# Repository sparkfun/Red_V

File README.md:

SparkFun RED-V RedBoard
============================

*[SparkFun RED-V RedBoard (DEV-15594)](https://www.sparkfun.com/products/15594)*

The SparkFun RED-V (pronounced “red-five”) RedBoard is a low-cost, development board featuring the Freedom E310 SoC which brings with it the RISC-V instruction set architecture (ISA). What sets the RED-V RedBoard apart from the rest is the completely open-source approach from hardware to ISA. That means anyone can make full use the microcontroller without requiring royalties, licenses, or non-disclosure agreements. 

The RED-V RedBoard comes in the familiar Arduino Uno R3 form factor and includes the SiFive Freedom E310 core, 32MB of QSPI flash, an NXP K22 ARM Cortex-M4 for USB connectivity and operating as a JTAG interface, and a Qwiic connector to make I<sup>2</sup>C easy. The modern USB-C connector makes it easy to program and for more advanced users who prefer to use the power and speed of professional tools, we've also exposed the JTAG connector. Additionally, it comes programmed with a simple bootloader making the RED-V the best way to start prototyping and developing your RISC‑V applications. 

The on board Freedom E310 (FE310) is the first member of the Freedom Everywhere family of customizable SoCs from SiFive. Designed for microcontroller, embedded, IoT, and wearable applications, the FE310 features SiFive’s E31 CPU Coreplex, a high-performance, 32-bit RV32IMAC core. Running at 320+ MHz, the FE310 is among the fastest microcontrollers in the market. Additional features include a 16KB L1 Instruction Cache, a 16KB Data SRAM scratchpad, hardware multiply/divide, a debug module, flexible clock generation with on-chip oscillators and PLLs, and a wide variety of peripherals including UARTs, QSPI, PWMs, and timers. Multiple power domains and a low-power standby mode ensure a wide variety of applications can benefit from the FE310. The RED-V requires Freedom Studio software or a Zephyr RTOS build environment set up to program the board and interface with it.

Repository Contents
-------------------
* **/Hardware** - Eagle design files (.brd, .sch)
* **/Production** - Production panel files (.brd)

Documentation
--------------
* **[Hookup Guide](https://learn.sparkfun.com/tutorials/red-v-redboard-hookup-guide)** - Basic hookup guide for the RedBoard.
* **[RED-V Development Guide](https://learn.sparkfun.com/tutorials/red-v-development-guide)** - Getting started with the RED-V in Freedom Studio and Zephyr RTOS.

License Information
-------------------

This product is _**open source**_! 

Please review the LICENSE.md file for license information. 

If you have any questions or concerns on licensing, please contact techsupport@sparkfun.com.

Distributed as-is; no warranty is given.

- Your friends at SparkFun.

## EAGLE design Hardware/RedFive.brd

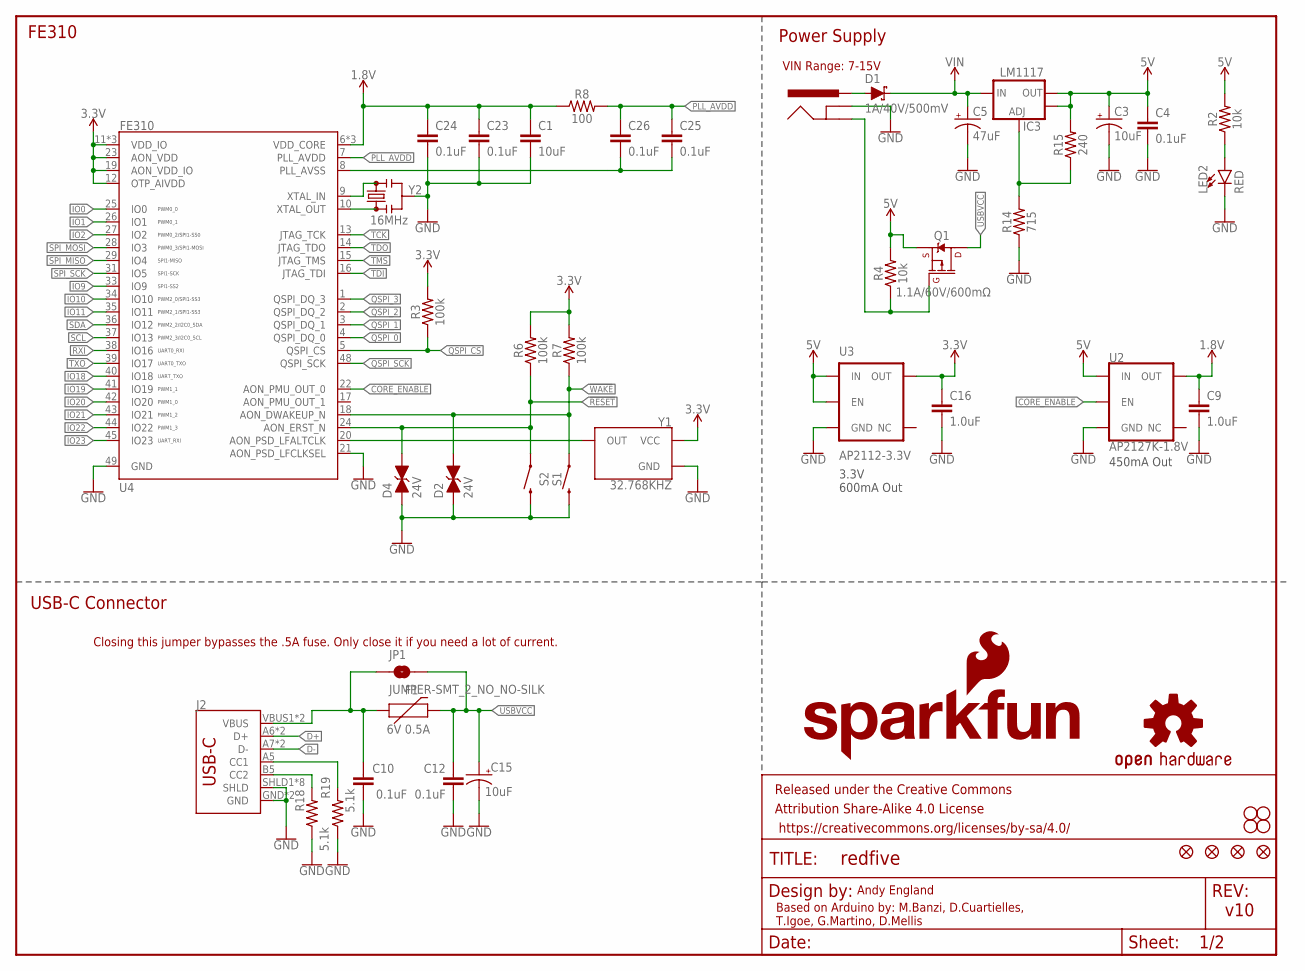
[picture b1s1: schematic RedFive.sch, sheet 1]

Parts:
C1: 10uF; 0603
C3, C15: 10uF; EIA3216
C4, C10, C12, C23, C24, C25, C26: 0.1uF; 0603
C5: 47uF; PANASONIC_D
C9, C16: 1.0uF; 0603
D1: 1A/40V/500mV; SMA-DIODE
D2, D4: 24V; 0603
F1: 6V 0.5A; 0805
FRAME2: FRAME-LETTER; CREATIVE_COMMONS
IC3: LM1117; SOT223-ALT1
J2: USB Female Type C Connector; USB-C-16P
J3: POWER_JACKSUPER_BOMB_DIGITY; POWER_JACK_SMD_OVERPASTE_SUPER_BOMB_DIGITY
JP1: JUMPER-SMT_2_NO_NO-SILK; SMT-JUMPER_2_NO_NO-SILK
JP3, JP4, JP5, JP6: STAND-OFF
JP8, JP9, JP15, JP16: FIDUCIAL1X2; FIDUCIAL-1X2
LED2: RED; LED-1206
LOGO1: SFE_LOGO_NAME_FLAME.1_INCH; SFE_LOGO_NAME_FLAME_.1
Q1: 1.1A/60V/600mΩ; SOT23-3
R2, R4: 10k; 0603
R3, R6, R7: 100k; 0603
R8: 100; 0603
R14: 715; 0603
R15: 240; 0603
R18, R19: 5.1k; 0603
S1, S2: MOMENTARY-SWITCH-SPST-SMD-6.2MM-TALL; TACTILE_SWITCH_SMD_6.2MM_TALL
U2: AP2127K-1.8V; SOT23-5
U3: AP2112-3.3V; SOT23-5
U4: FE310; QFN-48-.4MMPITCH
U$16: OSHW-LOGOS; OSHW-LOGO-S
Y1: 32.768KHZ; CRYSTAL-SMD-2X1.2MM
Y2: 16MHz; RESONATOR-SMD-3.2X1.3

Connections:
1.8V: C1.1, C9.1, C23.1, C24.1, R8.1, U2.5 (OUT), U4.6 (VDD_CORE), U4.30 (VDD_CORE), U4.46 (VDD_CORE)
3.3V: C16.1, R3.2, R6.2, R7.2, U3.5 (OUT), U4.11 (VDD_IO), U4.12 (OTP_AIVDD), U4.19 (AON_VDD_IO), U4.23 (AON_VDD), U4.32 (VDD_IO), U4.47 (VDD_IO), Y1.4 (VCC); also elsewhere on the board
5V: C3.+, C4.1, IC3.2 (OUT), IC3.4 (OUT), Q1.2 (S), R2.2, R4.2, R15.2, U2.1 (IN), U3.1 (IN), U3.3 (EN); also elsewhere on the board
!RESET: D4.2 (C), R6.1, S2.A2 (1), U4.24 (AON_ERST_N); also elsewhere on the board
!WAKE: D2.2 (C), R7.1, S1.A2 (1), U4.18 (AON_DWAKEUP_N); also elsewhere on the board
CORE_ENABLE: U2.3 (EN), U4.22 (AON_PMU_OUT_0)
D+: J2.A6 (D+), J2.B6 (D+); also elsewhere on the board
D-: J2.A7 (D-), J2.B7 (D-); also elsewhere on the board
GND: C1.2, C3.-, C4.2, C5.-, C9.2, C10.2, C12.2, C15.-, C16.2, C23.2, C24.2, D2.1 (A), D4.1 (A), J2.GND, J2.GND2 (GND), J2.SHLD1 (SHLD), J2.SHLD2 (SHLD), J2.SHLD3 (SHLD), J2.SHLD4 (SHLD), J2.SHLD5 (SHLD), J2.SHLD6 (SHLD), J2.SHLD7 (SHLD), J2.SHLD8 (SHLD), J3.GND (GNDBREAK), LED2.C, R14.1, R18.1, R19.1, S1.B2 (2), S2.B2 (2), U2.2 (GND), U3.2 (GND), U4.21 (AON_PSD_LFCLKSEL), U4.49 (GND), Y1.2 (GND), Y2.2; also elsewhere on the board
INSERT: J3.P$4 (GND), Q1.1 (G), R4.1
IO0: U4.25 (IO0); also elsewhere on the board
IO1: U4.26 (IO1); also elsewhere on the board
IO2: U4.27 (IO2); also elsewhere on the board
IO9: U4.33 (IO9); also elsewhere on the board
IO10: U4.34 (IO10); also elsewhere on the board
IO11: U4.35 (IO11); also elsewhere on the board
IO18: U4.40 (IO18); also elsewhere on the board
IO19: U4.41 (IO19); also elsewhere on the board
IO20: U4.42 (IO20); also elsewhere on the board
IO21: U4.43 (IO21); also elsewhere on the board
IO22: U4.44 (IO22); also elsewhere on the board
IO23: U4.45 (IO23); also elsewhere on the board
unnamed: LED2.A, R2.1
unnamed: U4.10 (XTAL_OUT), Y2.1
unnamed: U4.9 (XTAL_IN), Y2.3
unnamed: U4.20 (AON_PSD_LFALTCLK), Y1.3 (OUT)
unnamed: C25.2, C26.2, U4.8 (PLL_AVSS)
unnamed: J2.B5 (CC2), R18.2
unnamed: IC3.1 (ADJ), R14.2, R15.1
unnamed: J2.A5 (CC1), R19.2
PLL_AVDD: C25.1, C26.1, R8.2, U4.7 (PLL_AVDD)
PWRIN: D1.A, J3.VIN0 (PWR)
QSPI_0: U4.4 (QSPI_DQ_0); also elsewhere on the board
QSPI_1: U4.3 (QSPI_DQ_1); also elsewhere on the board
QSPI_2: U4.2 (QSPI_DQ_2); also elsewhere on the board
QSPI_3: U4.1 (QSPI_DQ_3); also elsewhere on the board
QSPI_CS: R3.1, U4.5 (QSPI_CS); also elsewhere on the board
QSPI_SCK: U4.48 (QSPI_SCK); also elsewhere on the board
RXI: U4.38 (IO16); also elsewhere on the board
SCL: U4.37 (IO13); also elsewhere on the board
SDA: U4.36 (IO12); also elsewhere on the board
SPI_MISO: U4.29 (IO4); also elsewhere on the board
SPI_MOSI: U4.28 (IO3); also elsewhere on the board
SPI_SCK: U4.31 (IO5); also elsewhere on the board
TCK: U4.13 (JTAG_TCK); also elsewhere on the board
TDI: U4.16 (JTAG_TDI); also elsewhere on the board
TDO: U4.14 (JTAG_TDO); also elsewhere on the board
TMS: U4.15 (JTAG_TMS); also elsewhere on the board
TXO: U4.39 (IO17); also elsewhere on the board
USBVCC: C12.1, C15.+, F1.2, JP1.2, Q1.3 (D)
VIN: C5.+, D1.C, IC3.3 (IN); also elsewhere on the board
VUSB: C10.1, F1.1, J2.VBUS1 (VBUS), J2.VBUS2 (VBUS), JP1.1

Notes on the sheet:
Power Supply
FE310
USB-C Connector
Based on Arduino by: M.Banzi, D.Cuartielles, T.Igoe, G.Martino, D.Mellis
Andy England
v10
VIN Range: 7-15V
3.3V 600mA Out
450mA Out
Closing this jumper bypasses the .5A fuse. Only close it if you need a lot of current.

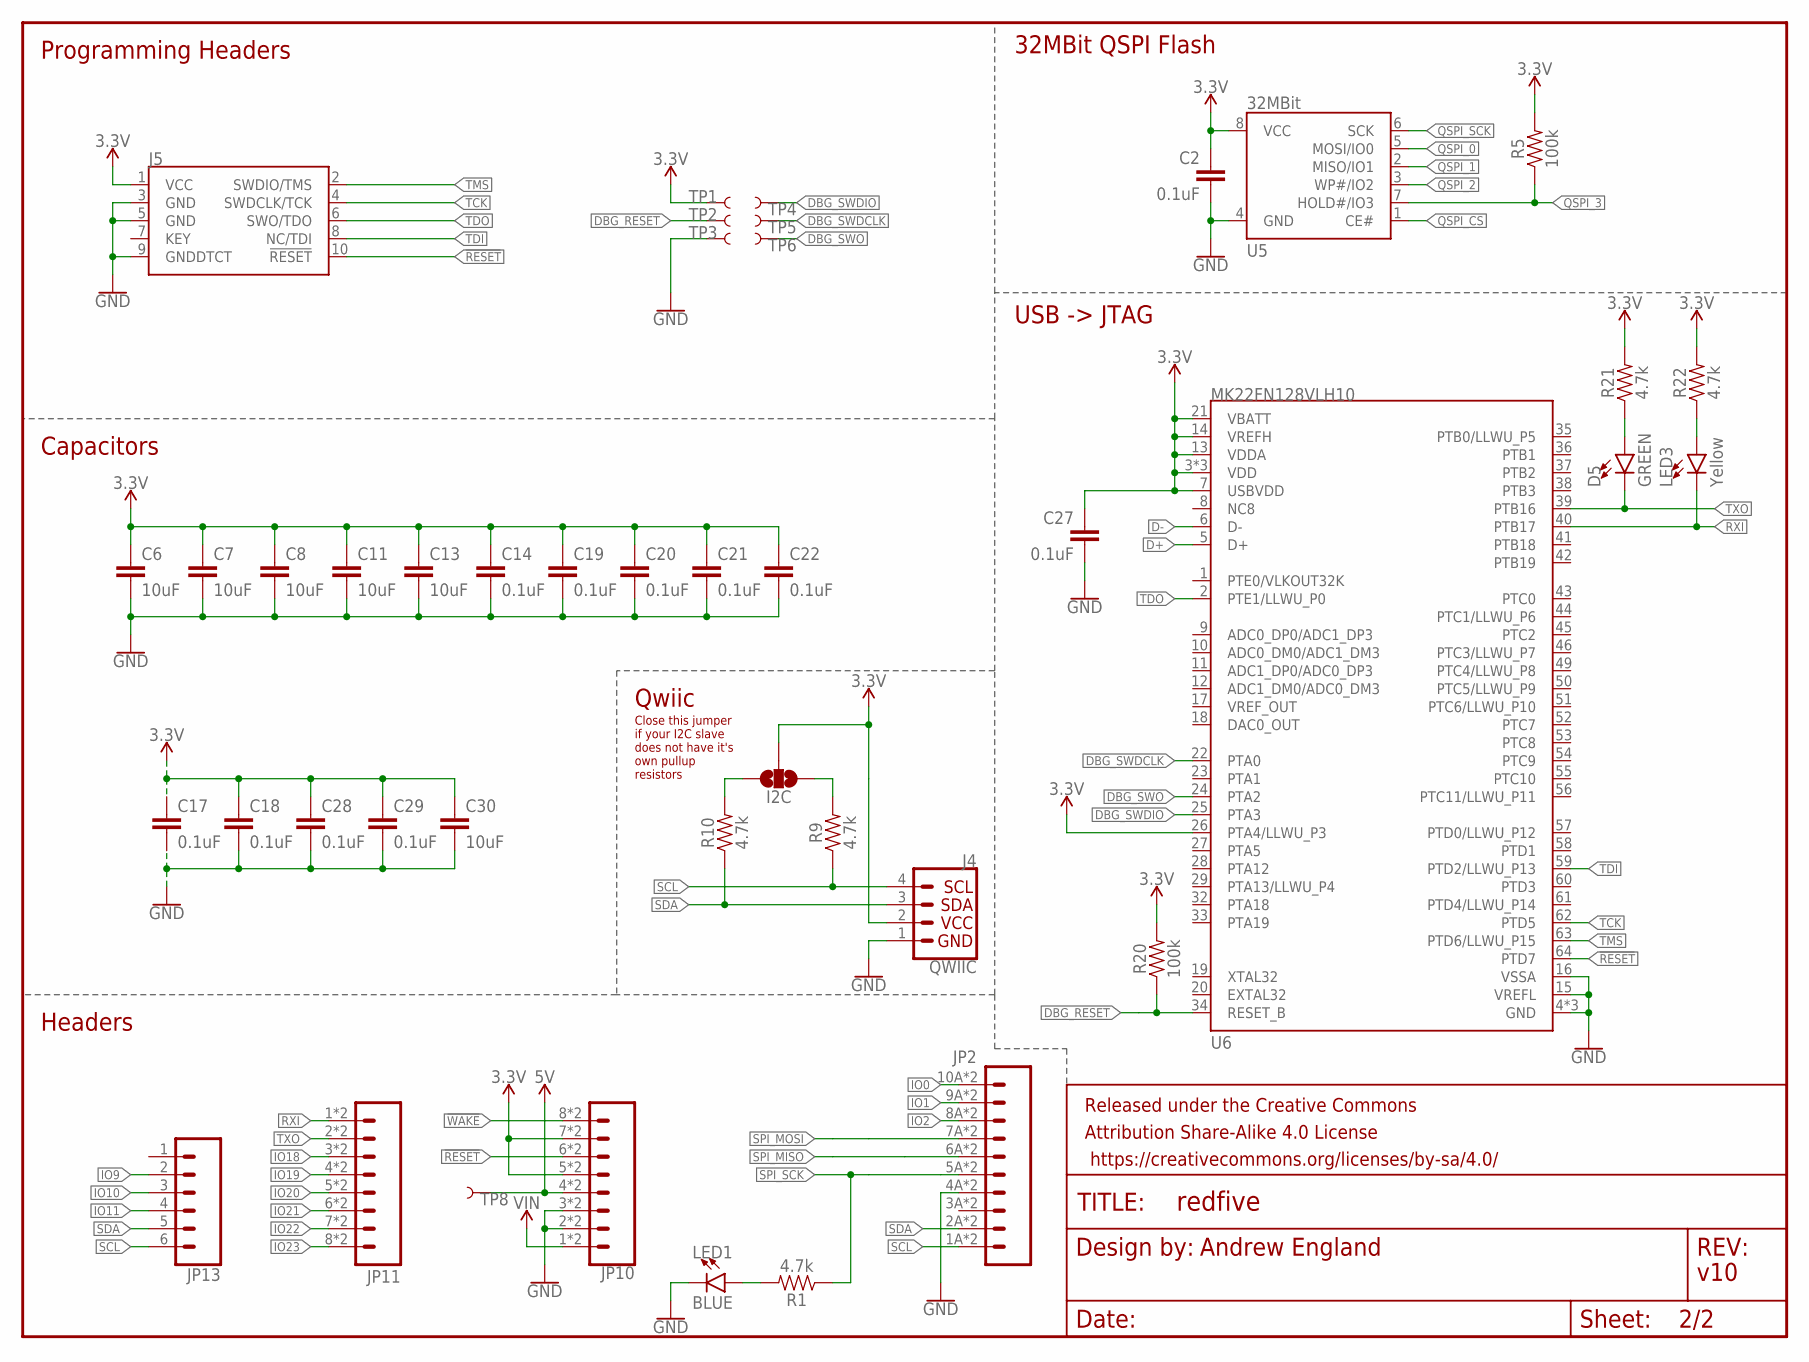
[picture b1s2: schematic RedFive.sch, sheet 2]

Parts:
C2, C14, C17, C18, C19, C20, C21, C22, C27, C28, C29: 0.1uF; 0603
C6, C7, C8, C11, C13, C30: 10uF; 0603
D5: GREEN; LED-1206
FRAME1: FRAME-LETTER; CREATIVE_COMMONS
I2C: JUMPER-SMT_3_NO_NO-SILK; SMT-JUMPER_3_NO_NO-SILK
J4: QWIIC; JST04_1MM_RA
J5: CORTEX_JTAG_DEBUG_PTH_NS; 2X5-PTH-1.27MM-NO_SILK
JP2: CONN_10SMD_COMBO-FEMALE; 1X10_SMD_COMBINED
JP10: CONN_08SMD-COMBO-FEMALE; 1X08_SMD_COMBINED
JP11: JP11; 1X08_SMD_COMBINED
JP13: CONN_06SMD-STRAIGHT-COMBO-FEMALE; 1X06_SMD_STRAIGHT_COMBO
LED1: BLUE; LED-1206
LED3: Yellow; LED-1206
R1, R9, R10, R21, R22: 4.7k; 0603
R5, R20: 100k; 0603
TP1, TP2, TP3, TP4, TP5, TP6: TEST-POINT3X5; PAD.03X.05
TP8: TEST-POINT3; PAD.03X.03
U5: 32MBit; SO08
U6: MK22FN128VLH10; LQFP-64

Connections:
3.3V: C2.1, C6.1, C7.1, C8.1, C11.1, C13.1, C14.1, C17.1, C18.1, C19.1, C20.1, C21.1, C22.1, C27.1, C28.1, C29.1, C30.1, I2C.2, J4.2, J5.1 (VCC), JP10.5, JP10.5@2 (5), JP10.7, JP10.7@2 (7), R5.2, R20.2, R21.2, R22.2, TP1.P$1, U5.8 (VCC), U6.3 (VDD), U6.7 (USBVDD), U6.13 (VDDA), U6.14 (VREFH), U6.21 (VBATT), U6.26 (PTA4/LLWU_P3), U6.30 (VDD), U6.48 (VDD); also elsewhere on the board
5V: JP10.4, JP10.4@2 (4), TP8.P$1; also elsewhere on the board
!RESET: J5.10 (!RESET), JP10.6, JP10.6@2 (6), U6.64 (PTD7); also elsewhere on the board
!WAKE: JP10.8, JP10.8@2 (8); also elsewhere on the board
D+: U6.5 (D+); also elsewhere on the board
D-: U6.6 (D-); also elsewhere on the board
DBG_RESET: R20.1, TP2.P$1, U6.34 (RESET_B)
DBG_SWDCLK: TP5.P$1, U6.22 (PTA0)
DBG_SWDIO: TP4.P$1, U6.25 (PTA3)
DBG_SWO: TP6.P$1, U6.24 (PTA2)
GND: C2.2, C6.2, C7.2, C8.2, C11.2, C13.2, C14.2, C17.2, C18.2, C19.2, C20.2, C21.2, C22.2, C27.2, C28.2, C29.2, C30.2, J4.1, J5.3 (GND), J5.5 (GND), J5.9 (GNDDTCT), JP2.4A (4), JP2.4B (4), JP10.2, JP10.2@2 (2), JP10.3, JP10.3@2 (3), LED1.C, TP3.P$1, U5.4 (GND), U6.4 (GND), U6.15 (VREFL), U6.16 (VSSA), U6.31 (GND), U6.47 (GND); also elsewhere on the board
IO0: JP2.10A (10), JP2.10B (10); also elsewhere on the board
IO1: JP2.9A (9), JP2.9B (9); also elsewhere on the board
IO2: JP2.8A (8), JP2.8B (8); also elsewhere on the board
IO9: JP13.2; also elsewhere on the board
IO10: JP13.3; also elsewhere on the board
IO11: JP13.4; also elsewhere on the board
IO18: JP11.3, JP11.3@2 (3); also elsewhere on the board
IO19: JP11.4, JP11.4@2 (4); also elsewhere on the board
IO20: JP11.5, JP11.5@2 (5); also elsewhere on the board
IO21: JP11.6, JP11.6@2 (6); also elsewhere on the board
IO22: JP11.7, JP11.7@2 (7); also elsewhere on the board
IO23: JP11.8, JP11.8@2 (8); also elsewhere on the board
unnamed: LED1.A, R1.2
unnamed: I2C.3, R10.2
unnamed: I2C.1, R9.2
unnamed: LED3.A, R22.1
unnamed: D5.A, R21.1
QSPI_0: U5.5 (MOSI/IO0); also elsewhere on the board
QSPI_1: U5.2 (MISO/IO1); also elsewhere on the board
QSPI_2: U5.3 (WP#/IO2); also elsewhere on the board
QSPI_3: R5.1, U5.7 (HOLD#/IO3); also elsewhere on the board
QSPI_CS: U5.1 (CE#); also elsewhere on the board
QSPI_SCK: U5.6 (SCK); also elsewhere on the board
RXI: JP11.1, JP11.1@2 (1), LED3.C, U6.40 (PTB17); also elsewhere on the board
SCL: J4.4, JP2.1A (1), JP2.1B (1), JP13.6, R9.1; also elsewhere on the board
SDA: J4.3, JP2.2A (2), JP2.2B (2), JP13.5, R10.1; also elsewhere on the board
SPI_MISO: JP2.6A (6), JP2.6B (6); also elsewhere on the board
SPI_MOSI: JP2.7A (7), JP2.7B (7); also elsewhere on the board
SPI_SCK: JP2.5A (5), JP2.5B (5), R1.1; also elsewhere on the board
TCK: J5.4 (SWDCLK/TCK), U6.62 (PTD5); also elsewhere on the board
TDI: J5.8 (NC/TDI), U6.59 (PTD2/LLWU_P13); also elsewhere on the board
TDO: J5.6 (SWO/TDO), U6.2 (PTE1/LLWU_P0); also elsewhere on the board
TMS: J5.2 (SWDIO/TMS), U6.63 (PTD6/LLWU_P15); also elsewhere on the board
TXO: D5.C, JP11.2, JP11.2@2 (2), U6.39 (PTB16); also elsewhere on the board
VIN: JP10.1, JP10.1@2 (1); also elsewhere on the board

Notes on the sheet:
Qwiic
Headers
Programming Headers
32MBit QSPI Flash
Capacitors
Andrew England
v10
USB -> JTAG
Close this jumper if your I2C slave does not have it's own pullup resistors

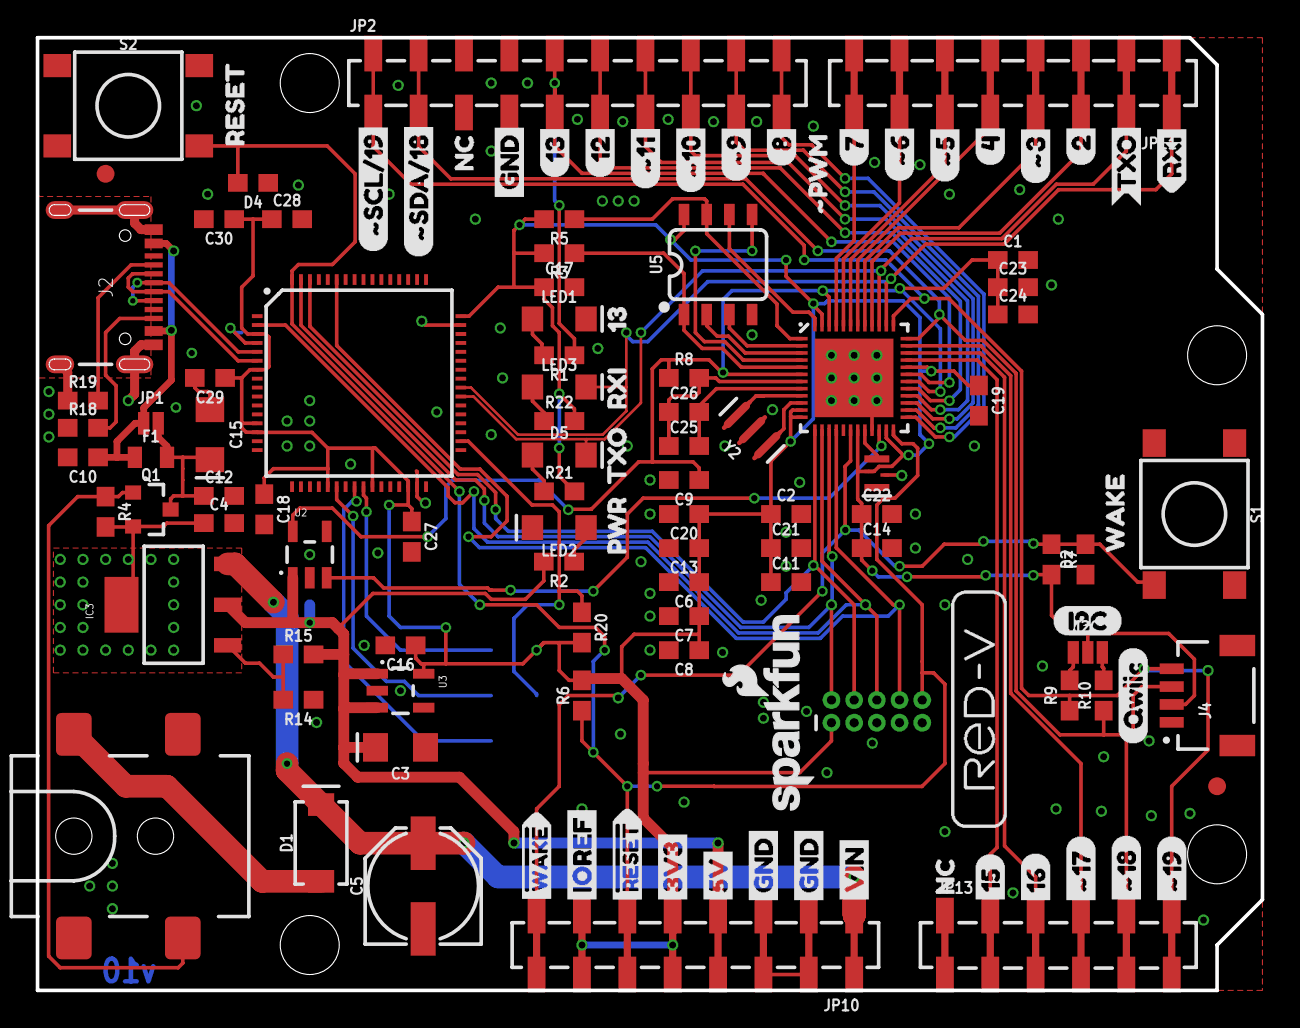
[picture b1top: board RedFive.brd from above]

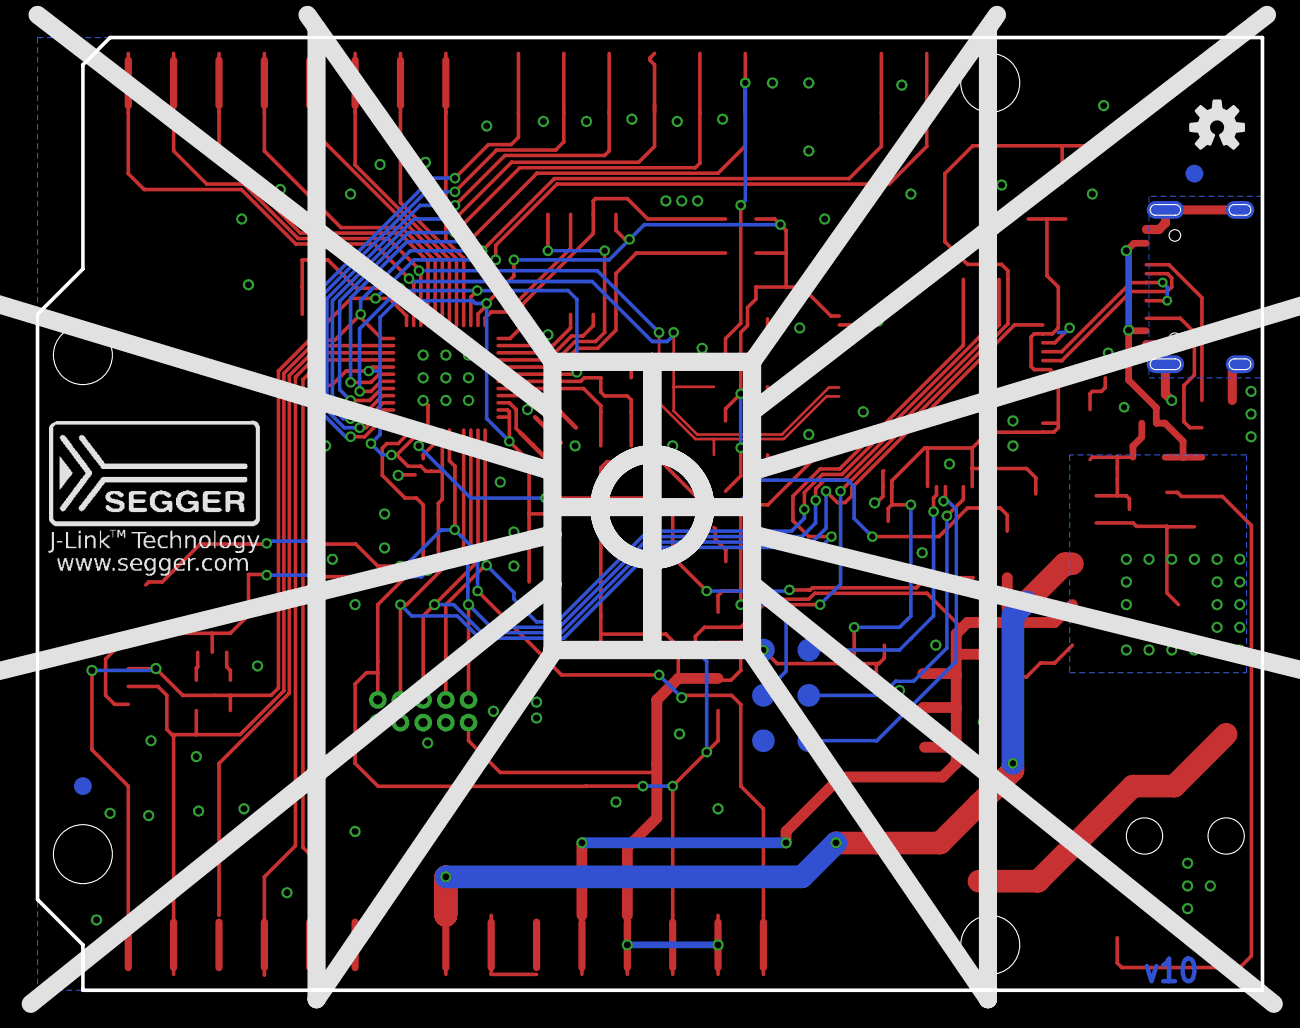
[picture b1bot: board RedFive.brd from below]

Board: 2 copper layers, 68.6 x 53.3 mm, 138 parts (11 on the bottom side), 61 nets.

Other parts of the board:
U$1: (QWIIC)
U$2: #324
U$3: #522
U$4: #621
U$8: SEGGERLOGO#PNG
U$9: #918
U$11: I2C0
U$14: #1017
U$15: #1116
U$17: #1710
U$18: #1812
U$19: #1911
U$20: #RESET2
U$21: #SCL#1926
U$22: #SDA#1827
U$23: #WAKE0
U$24: 3V33
U$25: 5V4
U$26: 158
U$27: 169
U$28: 225
U$29: 423
U$30: 720
U$31: 819
U$32: 1215
U$33: 1314
U$34, U$35, U$36: GND5
U$37: IOREF1
U$38, U$43: NC7
U$39: RXI29
U$40: TXO28
U$41: VIN6
U$42: _#PWM30
U$45: 133
U$46: PWR0
U$47: RXI1
U$48: TXO2
U$49: RESET0
U$50: WAKE1
U$52: REDFIVE_LOGO#05#PNG

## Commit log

2019-08-05 initial layout for proto
2019-08-06 pre review changes
2019-08-06 post review changes
2019-08-06 design review checklist
2019-08-06 ordered prototypes
2019-08-14 Adding prod_id to JTAG
2019-08-22 pre design review number 2
2019-08-22 small schematic tweaks, thanks pete for notes
2019-08-22 post design review changes
2019-08-22 post checklist changes, protos ordered
2019-09-18 updating Gerbers to v02 with NXP chip
2019-09-27 adding 5V test point
2019-10-09 needs routing, post prototype changes
2019-10-16 Pre design review-reds
2019-10-16 post review changes-v10
2019-10-16 post checklist changes
2019-12-10 updating R8 to 100 Ohm

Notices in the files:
parts and their libraries:
SparkFun-Aesthetics: Licensing: CC v3.0 Share-Alike You are welcome to use this library for commercial purposes.
SparkFun-Aesthetics: Released under the Creative Commons Attribution Share-Alike 4.0 License
SparkFun-Aesthetics: https://creativecommons.org/licenses/by-sa/4.0
